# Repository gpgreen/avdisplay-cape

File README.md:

# Avdisplay Cape

Kicad design for beaglebone black cape. Provides Dual CAN bus & bus
protection. Provides 4A of 5V power to the beaglebone black using dual
offboard 1.5A switching power supplies. These are load balanced using
a LTC4370 device. Since the project is also using a LCD display, only
one of the beaglebone's dual CAN devices is available due to pin
conflicts, so another external MCP2515 CAN controller connected via SPI is
onboard.

## Offboard power supplies

The design is intended to use two Sparkfun [buck boost power
supplies](https://www.sparkfun.com/products/15208) which use a
TPS63070 device. The input range is 3-16V. The project is supplied
from a 12V system. The output on the breakout boards is selected to 5V
and each device connected to the board with the provided JST
connectors. With a heatsink installed on each device, they are capable
of providing 2A for a total of 4A. The 12V input should have diode
protection and a fuse as those are not installed on either the
buck-boost breakout boards or the cape.

## View and Schematics

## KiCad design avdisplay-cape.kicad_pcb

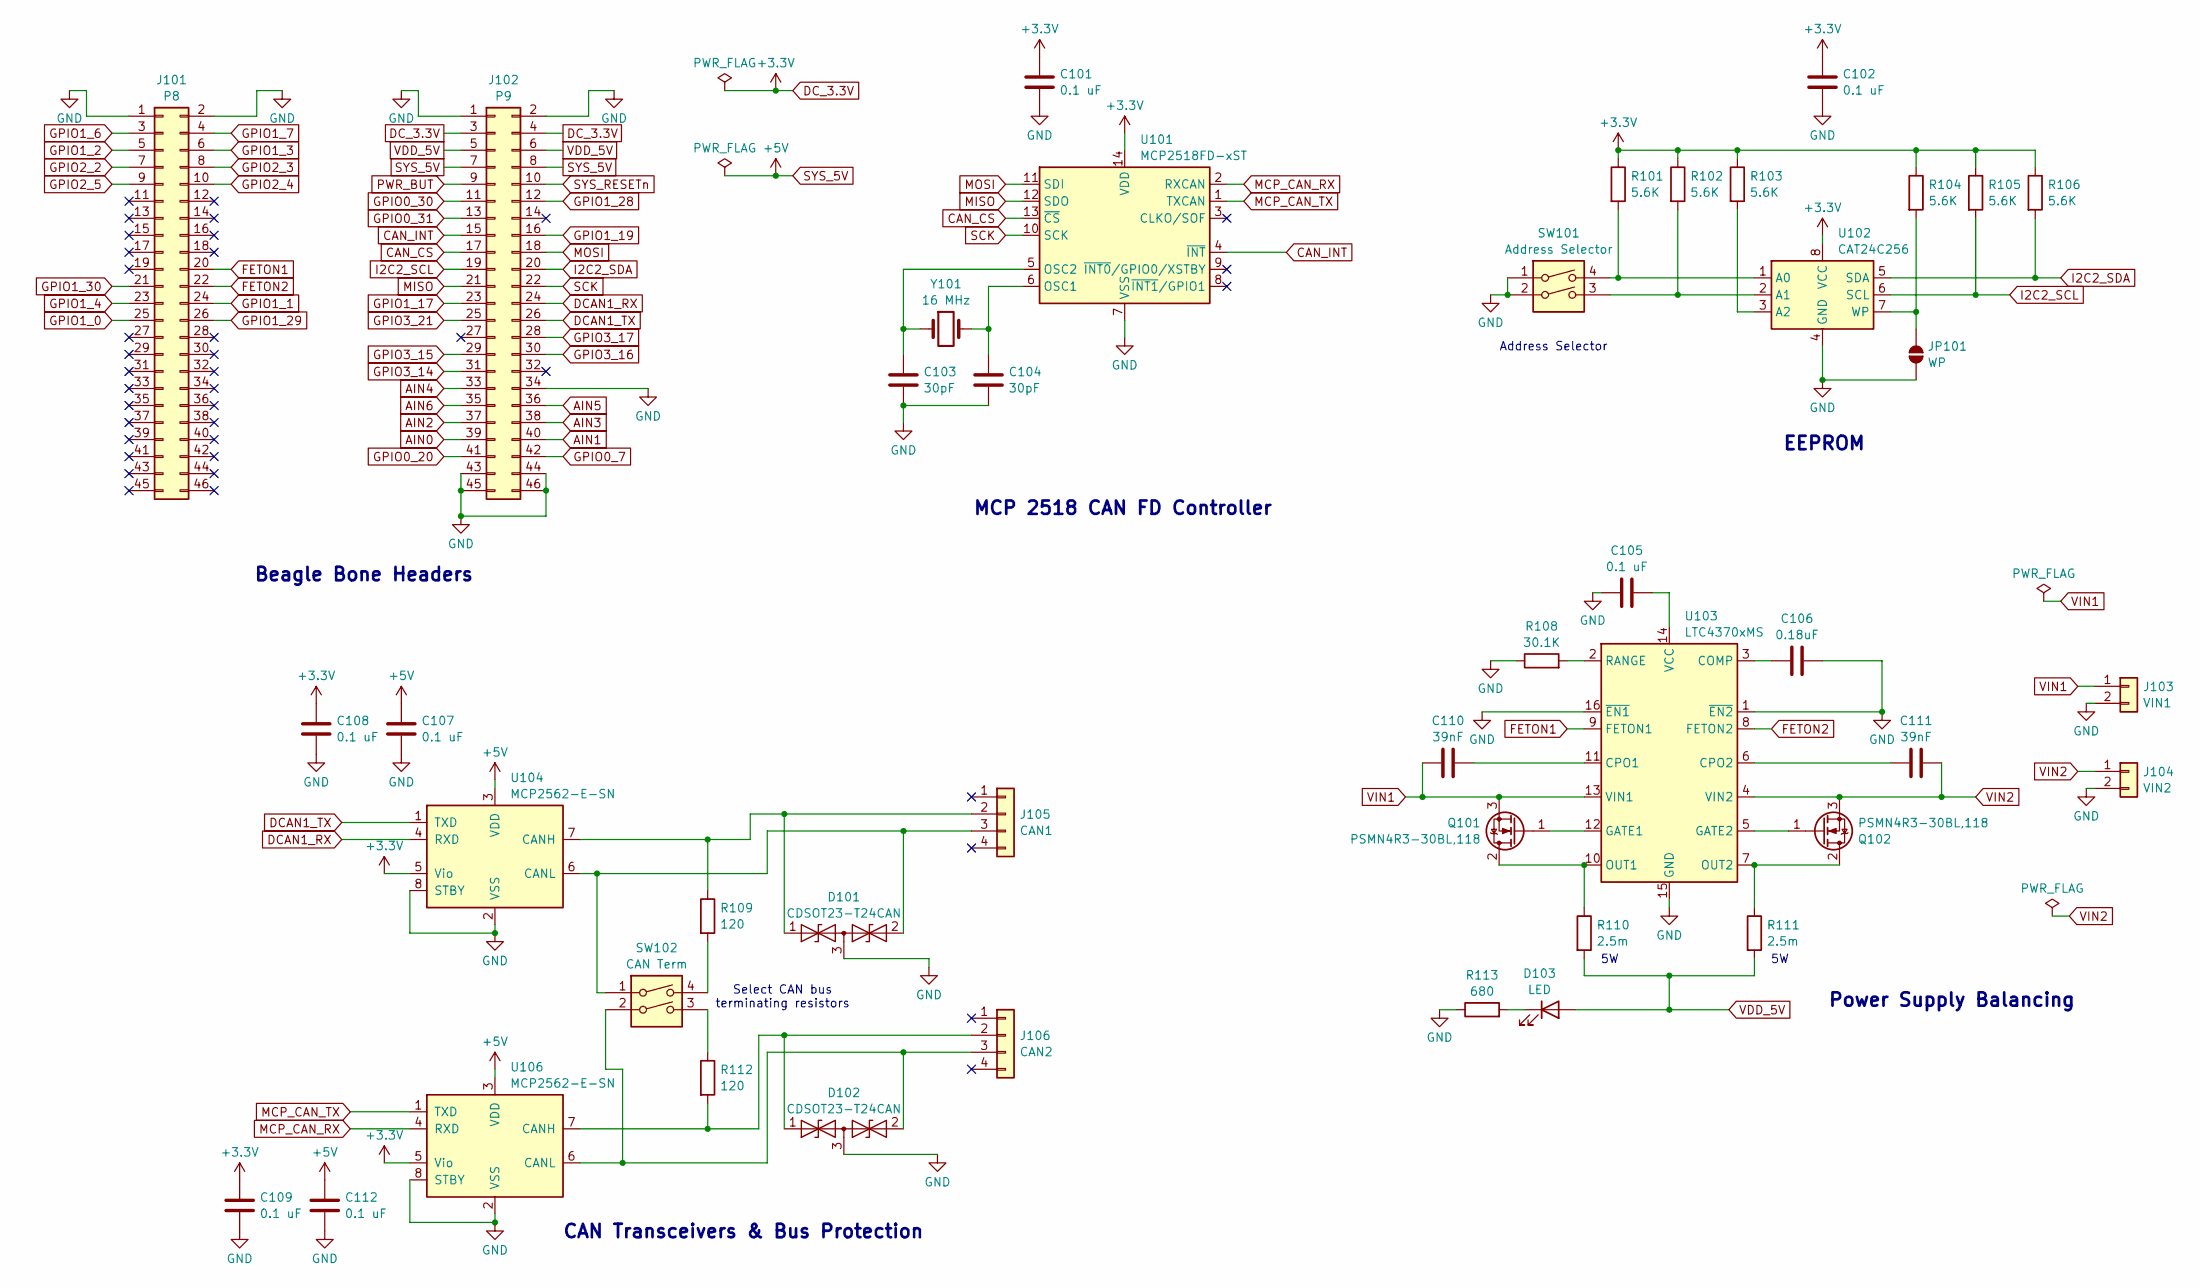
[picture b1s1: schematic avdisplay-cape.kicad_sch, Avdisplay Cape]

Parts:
C101, C102, C105, C107, C108, C109, C112: 0.1 uF; C_0603_1608Metric
C103, C104: 30pF; C_0603_1608Metric
C106: 0.18uF; C_0603_1608Metric
C110, C111: 39nF; C_0603_1608Metric
D101, D102: CDSOT23-T24CAN; SOT-23
D103: LED; LED_0603_1608Metric
J101: P8; PinHeader_2x23_P2.54mm_Vertical
J102: P9; PinHeader_2x23_P2.54mm_Vertical
J103: VIN1; Molex_KK-254_AE-6410-02A_1x02_P2.54mm_Vertical
J104: VIN2; Molex_KK-254_AE-6410-02A_1x02_P2.54mm_Vertical
J105: CAN1; JST_EH_B4B-EH-A_1x04_P2.50mm_Vertical
J106: CAN2; JST_EH_B4B-EH-A_1x04_P2.50mm_Vertical
JP101: WP; SolderJumper-2_P1.3mm_Open_Pad1.0x1.5mm
Q101, Q102: PSMN4R3-30BL,118; TO-263-2
R101, R102, R103, R104, R105, R106: 5.6K; R_0603_1608Metric
R108: 30.1K; R_0603_1608Metric
R109, R112: 120; R_1206_3216Metric
R110, R111: 2.5m; WSLP3921
R113: 680; R_0603_1608Metric
SW101: Address Selector; SW_DIP_SPSTx02_Slide_9.78x7.26mm_W7.62mm_P2.54mm
SW102: CAN Term; SW_DIP_SPSTx02_Slide_9.78x7.26mm_W7.62mm_P2.54mm
U101: MCP2518FD-xST; SOIC-14_3.9x8.7mm_P1.27mm
U102: CAT24C256; SOIC-8_3.9x4.9mm_P1.27mm
U103: LTC4370xMS; MSOP-16_3x4mm_P0.5mm
U104, U106: MCP2562-E-SN; SOIC-8_3.9x4.9mm_P1.27mm
Y101: 16 MHz; Crystal_SMD_HC49-SD

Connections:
AIN0: J102.39
AIN1: J102.40
AIN2: J102.37
AIN3: J102.38
AIN4: J102.33
AIN5: J102.36
AIN6: J102.35
CAN_CS: J102.17, U101.13 (~CS)
CAN_INT: J102.15, U101.4 (~INT)
DCAN1_RX: J102.24, U104.4 (RXD)
DCAN1_TX: J102.26, U104.1 (TXD)
DC_3.3V: C101.1, C102.1, C108.1, C109.1, J102.3, J102.4, R101.1, R102.1, R103.1, R104.1, R105.1, R106.1, U101.14 (VDD), U102.8 (VCC), U104.5 (Vio), U106.5 (Vio)
FETON1: J101.20, U103.9 (FETON1)
FETON2: J101.22, U103.8 (FETON2)
GND: C101.2, C102.2, C103.2, C104.2, C105.1, C106.2, C107.2, C108.2, C109.2, C112.2, D101.3 (common), D102.3 (common), J101.1, J101.2, J102.1, J102.2, J102.34, J102.43, J102.44, J102.45, J102.46, J103.2, J104.2, JP101.1 (A), R108.1, R113.1, SW101.1, SW101.2, U101.7 (VSS), U101.15 (VSS), U102.4 (GND), U103.1 (~EN2), U103.15 (GND), U103.16 (~EN1), U104.2 (VSS), U104.8 (STBY), U106.2 (VSS), U106.8 (STBY)
GPIO0_7: J102.42
GPIO0_20: J102.41
GPIO0_30: J102.11
GPIO0_31: J102.13
GPIO1_0: J101.25
GPIO1_1: J101.24
GPIO1_2: J101.5
GPIO1_3: J101.6
GPIO1_4: J101.23
GPIO1_6: J101.3
GPIO1_7: J101.4
GPIO1_17: J102.23
GPIO1_19: J102.16
GPIO1_28: J102.12
GPIO1_29: J101.26
GPIO1_30: J101.21
GPIO2_2: J101.7
GPIO2_3: J101.8
GPIO2_4: J101.10
GPIO2_5: J101.9
GPIO3_14: J102.31
GPIO3_15: J102.29
GPIO3_16: J102.30
GPIO3_17: J102.28
GPIO3_21: J102.25
I2C2_SCL: J102.19, R105.2, U102.6 (SCL)
I2C2_SDA: J102.20, R106.2, U102.5 (SDA)
MCP_CAN_RX: U101.2 (RXCAN), U106.4 (RXD)
MCP_CAN_TX: U101.1 (TXCAN), U106.1 (TXD)
MISO: J102.21, U101.12 (SDO)
MOSI: J102.18, U101.11 (SDI)
unnamed: D101.1 (A1), J105.2, R109.1, U104.7 (CANH)
unnamed: D101.2 (A2), J105.3, SW102.1, U104.6 (CANL)
unnamed: D102.1 (A1), J106.2, R112.2, U106.7 (CANH)
unnamed: D102.2 (A2), J106.3, SW102.2, U106.6 (CANL)
unnamed: D103.1 (K), R113.2
unnamed: JP101.2 (B), R104.2, U102.7 (WP)
unnamed: Q101.2 (D), R110.1, U103.10 (OUT1)
unnamed: Q101.1 (G), U103.12 (GATE1)
unnamed: Q102.2 (D), R111.1, U103.7 (OUT2)
unnamed: Q102.1 (G), U103.5 (GATE2)
unnamed: R109.2, SW102.4
unnamed: R112.1, SW102.3
unnamed: C104.1, U101.6 (OSC1), Y101.2
unnamed: C103.1, U101.5 (OSC2), Y101.1
unnamed: R101.2, SW101.4, U102.1 (A0)
unnamed: R102.2, SW101.3, U102.2 (A1)
unnamed: R103.2, U102.3 (A2)
unnamed: C106.1, U103.3 (COMP)
unnamed: C110.2, U103.11 (CPO1)
unnamed: C111.1, U103.6 (CPO2)
unnamed: R108.2, U103.2 (RANGE)
unnamed: C105.2, U103.14 (VCC)
PWR_BUT: J102.9
SCK: J102.22, U101.10 (SCK)
SYS_5V: C107.1, C112.1, J102.7, J102.8, U104.3 (VDD), U106.3 (VDD)
SYS_RESETn: J102.10
VDD_5V: D103.2 (A), J102.5, J102.6, R110.2, R111.2
VIN1: C110.1, J103.1, Q101.3 (S), U103.13 (VIN1)
VIN2: C111.2, J104.1, Q102.3 (S), U103.4 (VIN2)

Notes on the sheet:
EEPROM
Beagle Bone Headers
CAN Transceivers & Bus Protection
MCP 2518 CAN FD Controller
Power Supply Balancing
Select CAN bus terminating resistors
Address Selector

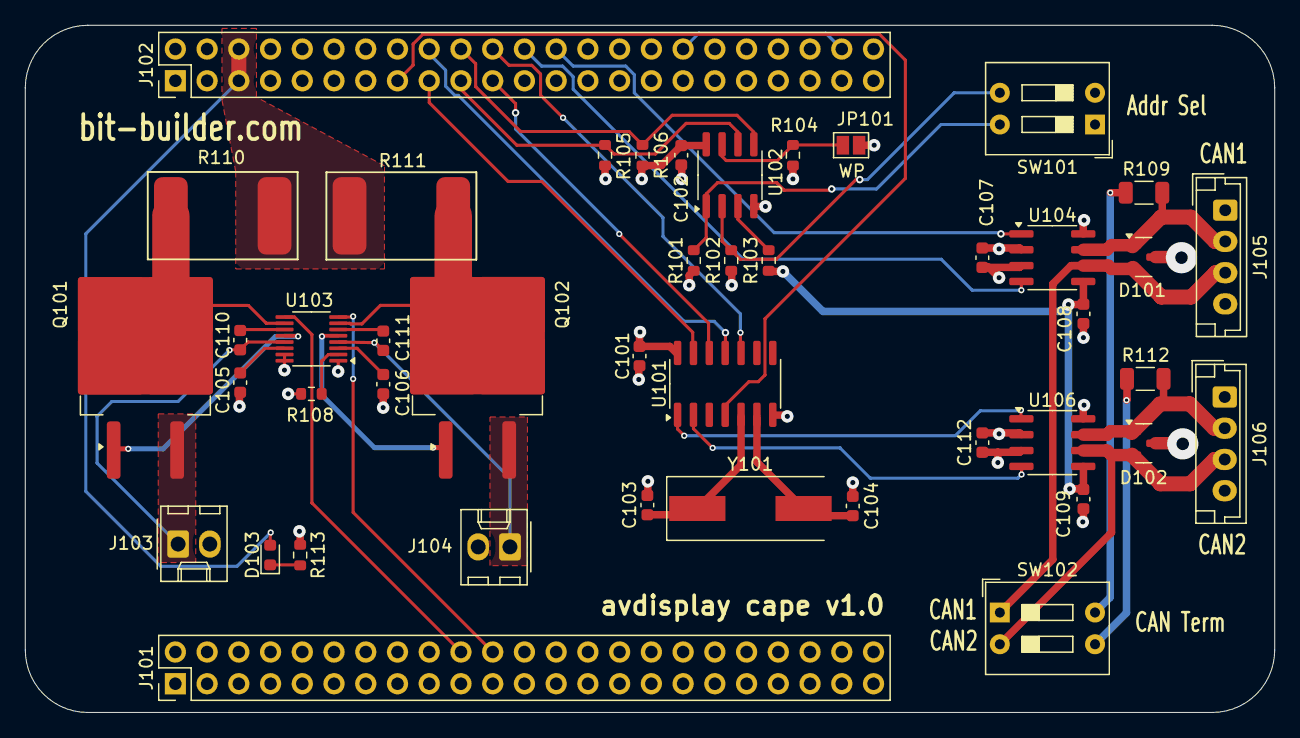
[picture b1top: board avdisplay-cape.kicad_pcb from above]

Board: 4 copper layers, 100.0 x 55.0 mm, 44 parts (0 on the bottom side), 41 nets.

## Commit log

2024-04-22 Updated image to show all
2024-05-27 First pass at mcp2518 version
